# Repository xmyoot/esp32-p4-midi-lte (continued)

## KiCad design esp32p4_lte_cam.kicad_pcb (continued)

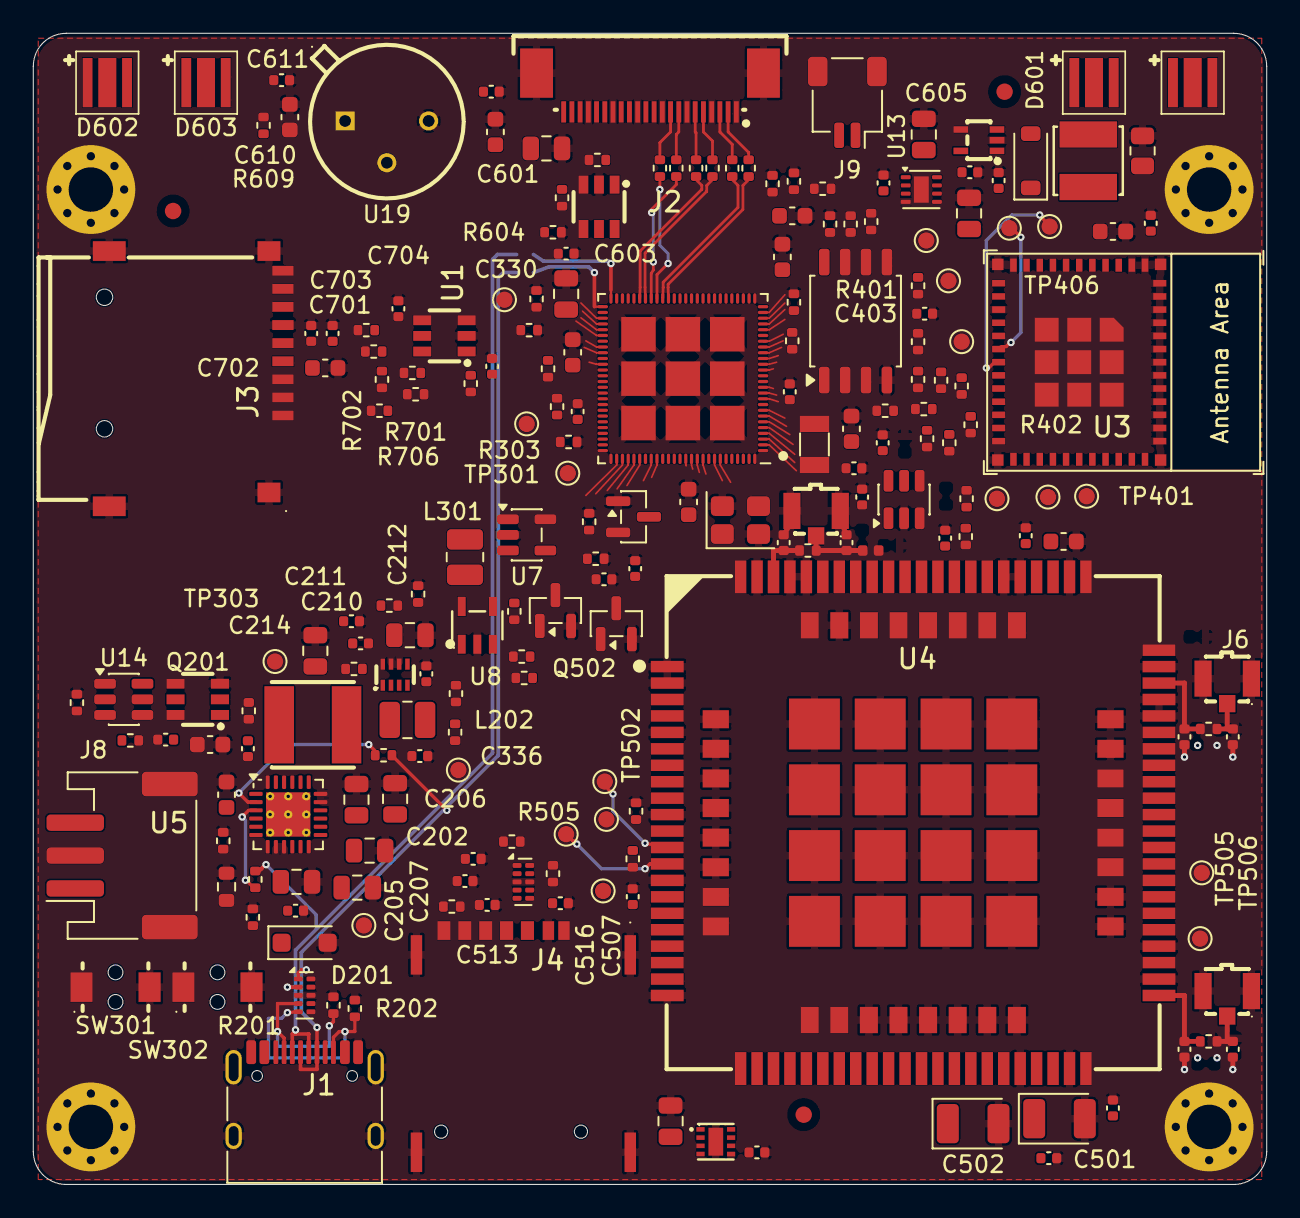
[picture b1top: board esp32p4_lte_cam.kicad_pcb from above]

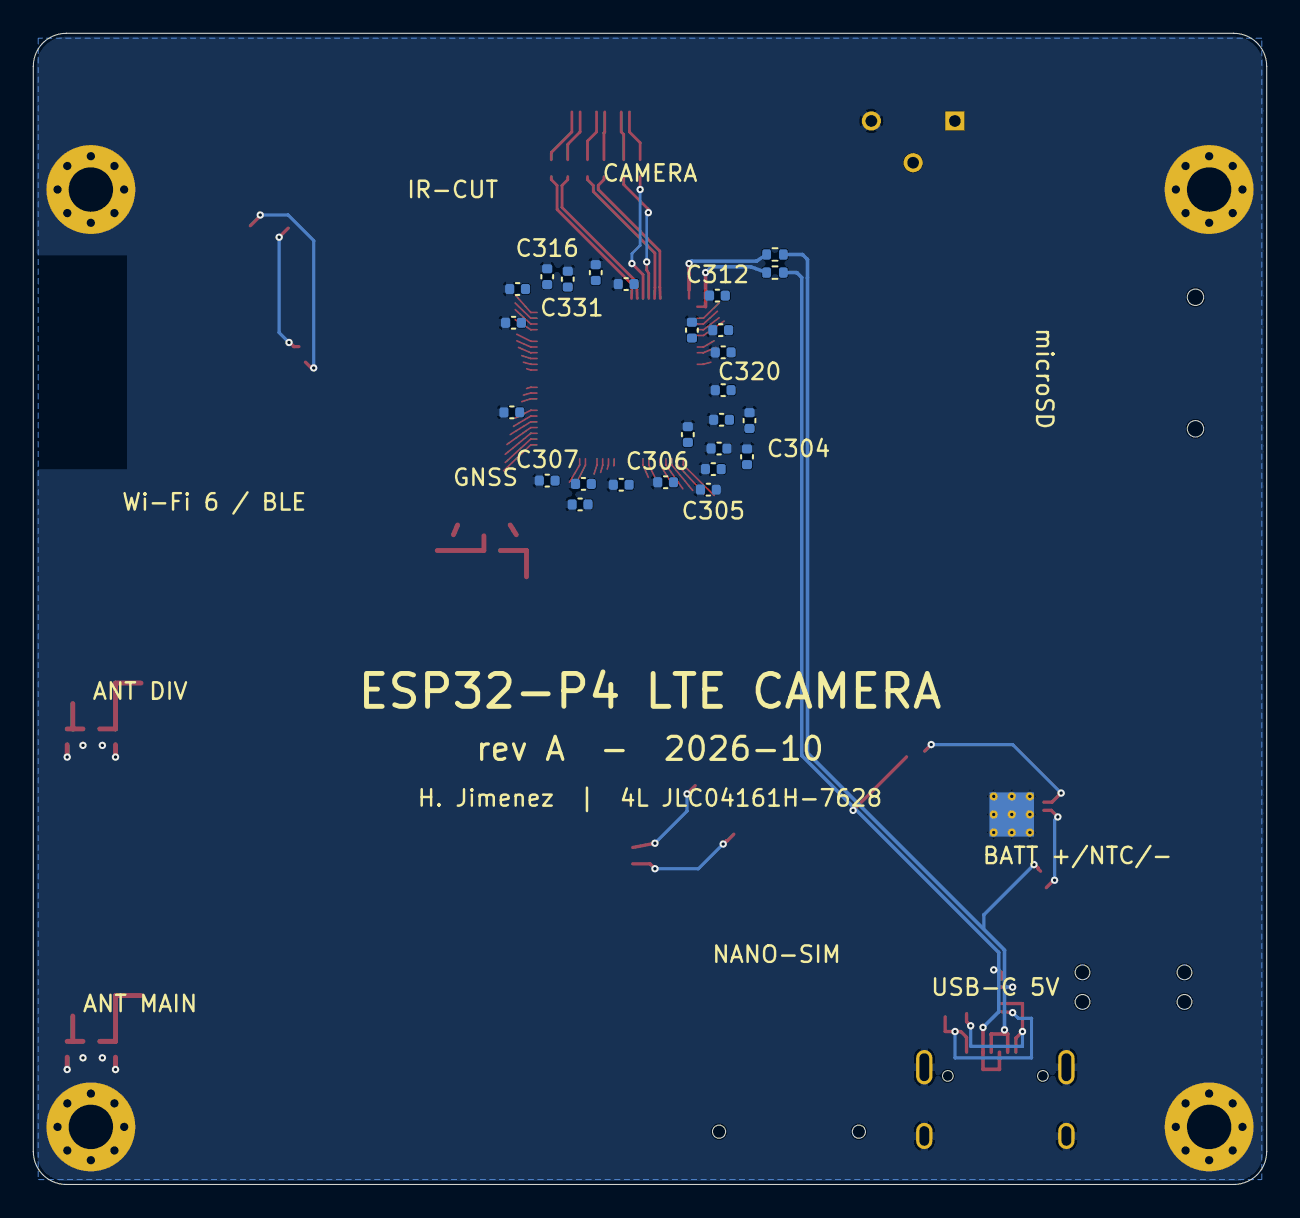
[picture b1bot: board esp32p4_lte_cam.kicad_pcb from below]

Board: 4 copper layers, 75.0 x 70.0 mm, 238 parts (26 on the bottom side), 160 nets.

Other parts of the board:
FID1, FID2, FID3: Fiducial; Fiducial_1mm_Mask2mm
H1, H2, H3, H4: M2.5; MountingHole_2.7mm_M2.5_Pad_Via

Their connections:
GND: H1.1, H2.1, H3.1, H4.1; also elsewhere on the board

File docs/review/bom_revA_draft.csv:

"Refs","Value","Footprint","LCSC","MPN","Qty","DNP"
"C201","1u 25V","Capacitor_SMD:C_0603_1608Metric","C5673","CL10A105KA8NNNC","1",""
"C202","10u 25V","Capacitor_SMD:C_0805_2012Metric","C15850","CL21A106KAYNNNE","1",""
"C203,C328,C610","4.7u 10V","Capacitor_SMD:C_0603_1608Metric","C1705","CL10A475KP8NNNC","3",""
"C204","47n 16V","Capacitor_SMD:C_0402_1005Metric","C307434","CL05B473KO5NNNC","1",""
"C205,C206,C207,C508,C605,C607","10u 10V","Capacitor_SMD:C_0805_2012Metric","C17024","CL21A106KPFNNNE","6",""
"C208,C213,C301,C302,C303,C304,C305,C306,C307,C311,C312,C313,C314,C317,C319,C320,C323,C326,C331,C336,C402,C504,C511,C512,C516,C602,C609,C611,C703","100n","Capacitor_SMD:C_0402_1005Metric","C1525","CL05B104KO5NNNC","29",""
"C209,C211,C212,C330","22u 10V","Capacitor_SMD:C_0805_2012Metric","C380338","TCC0805X5R226M100FT","4",""
"C214,C215,C316,C318,C321,C322,C325,C327,C403,C507,C604,C705","1u","Capacitor_SMD:C_0402_1005Metric","C52923","CL05A105KA5NQNC","12",""
"C308,C309,C310,C315,C401,C503,C601,C702","10u 10V","Capacitor_SMD:C_0603_1608Metric","C19702","CL10A106KP8NNNC","8",""
"C324","10n","Capacitor_SMD:C_0402_1005Metric","C15195","CL05B103KB5NNNC","1",""
"C329,C332,C333","22p","Capacitor_SMD:C_0402_1005Metric","C1555","0402CG220J500NT","3",""
"C334,C335","18p","Capacitor_SMD:C_0402_1005Metric","C1549","0402CG180J500NT","2",""
"C501,C502","220u 6.3V","Capacitor_Tantalum_SMD:CP_EIA-3528-21_Kemet-B","C30242","TLJB227M006R0500","2",""
"C505,C513,C514,C515","33p","Capacitor_SMD:C_0402_1005Metric","C1562","0402CG330J500NT","4",""
"C506","10p","Capacitor_SMD:C_0402_1005Metric","C32949","CL05C100JB5NNNC","1",""
"C509,C603,C704","1n 25V","Capacitor_SMD:C_0402_1005Metric","C541372","CC0402KRX7R8BB102","3",""
"C510,C608","100n 16V","Capacitor_SMD:C_0402_1005Metric","C1525","CL05B104KO5NNNC","2",""
"C606","4.7u 25V","Capacitor_SMD:C_0805_2012Metric","C1779","CL21A475KAQNNNE","1",""
"D201","SMF5.0A (TVS)","Diode_SMD:D_SOD-123F","C193402","SMF5.0A","1",""
"D601","B5819W","Diode_SMD:D_SOD-123","C8598","B5819W SL","1",""
"D602,D603,D604,D605","IR 850nm","lcsc:LED-SMD_3P-L3.8-W3.8_M3838E1IRS1G09","C2833567","M3838E1IRS1G09-850NM","4",""
"J1","USB-C (bottom edge)","Connector_USB:USB_C_Receptacle_HRO_TYPE-C-31-M-12","C165948","TYPE-C-31-M-12","1",""
"J2","CAM FPC 22P 0.5mm","lcsc:CONN-SMD_05B20L22P","C22459552","05B20L22P","1",""
"J3","microSD","lcsc:TF-SMD_TF-01A","C91145","TF-01A","1",""
"J4","Nano-SIM","lcsc:SIM-SMD_NANO-SIM-7P-H1.37","C7529384","NANO SIM 7P H1.37","1",""
"J5","U.FL MAIN","lcsc:RF-SMD_FRF05002-JSS103M","C88374","U.FL-R-SMT-1(80)","1",""
"J6","U.FL AUX","lcsc:RF-SMD_FRF05002-JSS103M","C88374","U.FL-R-SMT-1(80)","1",""
"J7","U.FL GNSS","lcsc:RF-SMD_FRF05002-JSS103M","C88374","U.FL-R-SMT-1(80)","1",""
"J8","BATT (+ / NTC / -)","Connector_JST:JST_PH_S3B-PH-SM4-TB_1x03-1MP_P2.00mm_Horizontal","C265101","S3B-PH-SM4-TB(LF)(SN)","1",""
"J9","IR-CUT","Connector_JST:JST_SH_SM02B-SRSS-TB_1x02-1MP_P1.00mm_Horizontal","C160402","SM02B-SRSS-TB(LF)(SN)","1",""
"L201","2.2uH","lcsc:IND-SMD_L5.0-W5.0_SMNR5030","C189797","SMNR5030-2R2N","1",""
"L202","1uH","Inductor_SMD:L_1008_2520Metric","C98348","WPN252012H1R0MT","1",""
"L301","2.2uH","Inductor_SMD:L_1008_2520Metric","C5832372","FTC252012S2R2MBCA","1",""
"L601","10uH","lcsc:IND-SMD_L4.0-W4.0","C38117","SWPA4030S100MT","1",""
"Q201","FS8205A","lcsc:SOT-23-6_L2.9-W1.6-P0.95-LS2.8-BR","C2830320","FS8205A","1",""
"Q501,Q502","2N7002","Package_TO_SOT_SMD:SOT-23","C8545","2N7002","2",""
"R201,R202","5.1k","Resistor_SMD:R_0402_1005Metric","C25905","0402WGF5101TCE","2",""
"R203,R204,R304,R305,R306,R307,R308,R309,R316,R317,R318,R319,R320,R321,R509,R510,R511","0","Resistor_SMD:R_0402_1005Metric","C17168","0402WGF0000TCE","17",""
"R205","120","Resistor_SMD:R_0402_1005Metric","C25079","0402WGF1200TCE","1",""
"R206","5.23k","Resistor_SMD:R_0402_1005Metric","C2933105","FRC0402F5231TS","1",""
"R207","30.1k","Resistor_SMD:R_0402_1005Metric","C29402","0402WGF3012TCE","1",""
"R208,R209,R210,R310,R312,R313,R401,R402,R403,R404,R405,R406,R407,R408,R508,R603,R702,R703,R704,R705,R706,R707","10k","Resistor_SMD:R_0402_1005Metric","C25744","0402WGF1002TCE","22",""
"R211,R609","100","Resistor_SMD:R_0402_1005Metric","C25076","0402WGF1000TCE","2",""
"R212,R311","1k","Resistor_SMD:R_0402_1005Metric","C11702","0402WGF1001TCE","2",""
"R213","560k","Resistor_SMD:R_0402_1005Metric","C137958","RC0402FR-07560KL","1",""
"R214,R501,R502,R503,R504,R605,R607,R608,R708","100k","Resistor_SMD:R_0402_1005Metric","C25741","0402WGF1003TCE","9",""
"R301","4.02k","Resistor_SMD:R_0402_1005Metric","C43251","0402WGF4021TCE","1",""
"R302,R303","499k","Resistor_SMD:R_0402_1005Metric","C2998054","FRC0402F4993TS","2",""
"R314,R315,R505,R506,R507,R701","22","Resistor_SMD:R_0402_1005Metric","C25092","0402WGF220JTCE","6",""
"R601,R602","2.2k","Resistor_SMD:R_0402_1005Metric","C25879","0402WGF2201TCE","2",""
"R606","0.68","Resistor_SMD:R_0805_2012Metric","C47389","0805W8F680LT5E","1",""
"SW301","RESET","lcsc:SW-SMD_L4.0-W2.9-P4.15-EH","C455278","TS-1088C-02026","1",""
"SW302","BOOT","lcsc:SW-SMD_L4.0-W2.9-P4.15-EH","C455278","TS-1088C-02026","1",""
"U1","ESP32-P4NRW32X","espressif:ESP32-P4","C54540373","ESP32-P4NRW32X","1",""
"U2","W25Q128JVSIQ","Package_SO:SOIC-8_5.3x5.3mm_P1.27mm","C97521","W25Q128JVSIQ","1",""
"U3","ESP32-C6-MINI-1","espressif:ESP32-C6-MINI-1","C5453904","ESP32-C6-MINI-1-N4","1",""
"U4","SIM7600G-H","lcsc:COMM-SMD_135P-L30.0-W30.0_SIM7600G","C5355477","SIM7600G-H","1",""
"U5","BQ25895RTWR","Package_DFN_QFN:Texas_RTW_WQFN-24-1EP_4x4mm_P0.5mm_EP2.7x2.7mm_ThermalVias","C80200","BQ25895RTWR","1",""
"U6","TPS631000","lcsc:SOT-583-8_L2.1-W1.2-P0.50-LS1.6-BL","C5219190","TPS631000DRLR","1",""
"U7","TLV62569","Package_TO_SOT_SMD:SOT-23-5","C141836","TLV62569DBVR","1",""
"U8","TPS7A0218","lcsc:SOT-23-5_L3.0-W1.7-P0.95-LS2.8-BL","C5144851","TPS7A0218DBVR","1",""
"U9","TPS22965","lcsc:UDFN-8_L2.0-W2.0-P0.50-TL-EP","C122837","TPS22965DSGR","1",""
"U10,U11","TPS22918","lcsc:SOT-23-6_L2.9-W1.6-P0.95-LS2.8-BR","C131941","TPS22918DBVR","2",""
"U12","TPS61169","lcsc:SC-70-5_L2.1-W1.3-P0.65-LS2.1-BR","C71045","TPS61169DCKR","1",""
"U13","DRV8837","Package_SON:Texas_DSG0008A_WSON-8-1EP_2x2mm_P0.5mm_EP0.9x1.6mm","C39159","DRV8837DSGR","1",""
"U14","DW01A","Package_TO_SOT_SMD:SOT-23-6","C351410","DW01A","1",""
"U15","TPS3839G33 (3.08V)","Package_TO_SOT_SMD:SOT-23","C485802","TPS3839G33DBZR","1",""
"U16","SN74LVC1T45","Package_TO_SOT_SMD:SOT-23-6","C7843","SN74LVC1T45DBVR","1",""
"U17,U18","TPD4E05U06","Package_SON:USON-10_2.5x1.0mm_P0.5mm","C138714","TPD4E05U06DQAR","2",""
"U19","XYC-PIR223D-S0","lcsc:TO-5-3_L8.2-W8.2","C2887901","XYC-PIR223D-S0","1",""
"Y1","40MHz 10ppm","Crystal:Crystal_SMD_3225-4Pin_3.2x2.5mm","C9010","X322540MPB4SI","1",""
"Y2","32.768kHz","Crystal:Crystal_SMD_3215-2Pin_3.2x1.5mm","C32346","Q13FC13500004","1",""

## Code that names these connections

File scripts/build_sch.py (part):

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s = D.sheet("mcu", "ESP32-P4 core - SoC, flash, clocks, core DC-DC, reset/boot")
s.notes += ["Chip rev v3.x (ESP32-P4NRW32X): VDD_HP_1 on pin 54; DC-DC feedback 499k/499k/22pF populated (HDG fig. 5).",
            "VDD_MIPI_DPHY fed from internal VDDO_3 (2.5 V) as on ESP32-P4-Function-EV v1.5.2. VDD_USBPHY unused (HS PHY not used).",
            "VDD_IO_6 = 1.8 V: GPIO49-54 talk to the SIM7600 UART natively. Keep these pins hi-Z while VBAT_LTE is off."]
u = s.add("U1", "espressif:ESP32-P4X", "ESP32-P4NRW32X", "espressif:ESP32-P4", LCSC="C54540373",
          MPN="ESP32-P4NRW32X", Note="Consigned - zero JLC stock at design time")
u.wire({  # power
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    "FLASH_CK": "P4_FL_CK", "FLASH_D": "P4_FL_D",
    "XTAL_N": "XTAL_N", "XTAL_P": "XTAL_P", "CHIP_PU": "CHIP_PU", "EN_DCDC": "EN_DCDC", "FB_DCDC": "FB_DCDC",
    # GPIO map (docs/ARCHITECTURE.md sec. 5)
    "GPIO0": "XTAL32_N", "GPIO1": "XTAL32_P", "GPIO2": "PIR_OUT", "GPIO3": "CHG_INT", "GPIO4": "MODEM_RI_3V3",
    "GPIO5": "SYS_SDA", "GPIO6": "SYS_SCL", "GPIO7": "MODEM_PWRKEY_CTL", "GPIO8": "MODEM_PWR_EN", "GPIO9": "C6_EN",
    "GPIO10": "C6_WAKE", "GPIO11": "MODEM_RESET_CTL", "GPIO12": "TP_GPIO12", "GPIO13": "TP_GPIO13",
    "GPIO14": "SDIO_D0", "GPIO15": "SDIO_D1", "GPIO16": "SDIO_D2", "GPIO17": "SDIO_D3", "GPIO18": "SDIO_CLK",
    "GPIO19": "SDIO_CMD", "GPIO20": "CAM_SDA", "GPIO21": "CAM_SCL", "GPIO22": "CAM_IO0", "GPIO23": "CAM_PWR_EN",
    "GPIO24": "P4_USB_DN", "GPIO25": "P4_USB_DP", "GPIO26": "C6_BOOT", "GPIO27": "IRCUT_NSLEEP",
    "GPIO28": "SD_PWR_EN", "GPIO29": "CAM_IO1", "GPIO30": "IRCUT_IN1", "GPIO31": "IRCUT_IN2", "GPIO32": "IR_LED_PWM",
    "GPIO33": "TP_GPIO33", "GPIO34": NC, "GPIO35": "BOOT", "GPIO36": NC, "GPIO37": "UART0_TX", "GPIO38": "UART0_RX",
    "GPIO39": "SD_D0", "GPIO40": "SD_D1", "GPIO41": "SD_D2", "GPIO42": "SD_D3", "GPIO43": "SD_CLK", "GPIO44": "SD_CMD",
    "GPIO45": "SD_DET", "GPIO46": NC, "GPIO47": NC, "GPIO48": NC,
    "GPIO49": "MDM_RXD", "GPIO50": "MDM_TXD", "GPIO51": "MDM_RTS", "GPIO52": "MDM_CTS", "GPIO53": "MDM_STATUS",
    "GPIO54": "MDM_DTR"})
# decoupling (HDG checklist sec. 1)
for net in ["3V3"] * 7:
    s.C("100n", net)
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s.R("22", "P4_USB_DP", "USB_DP"); s.R("22", "P4_USB_DN", "USB_DN")
for lane in ("D0_P", "D0_N", "CK_P", "CK_N", "D1_P", "D1_N"):
    s.R("0", f"P4_CSI_{lane}", f"CSI_{lane}")
for tp in ("UART0_TX", "UART0_RX", "BOOT", "CHIP_PU", "TP_GPIO12", "TP_GPIO13", "TP_GPIO33"):
    s.TP(tp)

# =====================================================================================  WIFI
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
# =====================================================================================  LTE
s = D.sheet("lte", "LTE Cat-4 + GNSS - SIM7600G-H, nano-SIM, antennas")
s.notes += ["VBAT_LTE from SYS via TPS22965 (16 mOhm). >=300 uF bulk at VBAT pins per SIMCom HW design sec. 3.1 (2 A GSM bursts).",
            "UART/STATUS/DTR are 1.8 V and connect straight to ESP32-P4 GPIO49-54 (VDD_IO_6 = 1V8_IO6).",
            "COEX1/COEX3/BOOT_CFG0 must not be pulled up before power-up -> left NC.  Pi-networks: series 0R, shunts DNP."]
u = s.add("U4", "lcsc:SIM7600G-H_C5355477", "SIM7600G-H", "lcsc:COMM-SMD_135P-L30.0-W30.0_SIM7600G", LCSC="C5355477",
          MPN="SIM7600G-H")
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
# =====================================================================================  STORAGE
s = D.sheet("storage", "microSD (SDMMC slot 0, 4-bit, 3.3 V) with power switch")
s.notes += ["SDMMC slot 0 fixed pins GPIO39-44; VDD_IO_5 at 3.3 V (no UHS-I). Pull-ups go to the switched rail 3V3_SD."]
s.add("J3", "lcsc:TF-01A", "microSD", "lcsc:TF-SMD_TF-01A", LCSC="C91145", MPN="TF-01A").wire(
    {"1": "SD_D2", "2": "SD_D3", "3": "SD_CMD", "4": "3V3_SD", "5": "SD_CLK_C", "6": "GND", "7": "SD_D0", "8": "SD_D1",
     "9": "SD_DET", "GND": "GND"})
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
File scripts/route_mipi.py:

"""Hand-designed MIPI CSI-2 routing (2 data lanes + clock), 100 ohm diff: w 0.17, s 0.13 (centres 0.30) on F.Cu over L2 GND.
Lane order differs between the ESP32-P4 (D1, CK, D0 with CK as N,P) and the Pi FPC (CK as P,N, D1, D0), and the P4 has no
documented lane/polarity remap, so the clock pair carries the crossover:
  CKP drops to B.Cu under its 0R (VP1); CKN crosses over it on F.Cu and drops (VN1); both run on B.Cu under the D1 pair,
  then return to F.Cu in a pocket between D1 and D0 (VN, VP, staggered) - now in P4 order (N left, P right).
D0 and D1 stay on F.Cu end to end.  Every coordinate below was clearance-checked against 0.127 mm; DRC verifies.
usage: $PY scripts/route_mipi.py board.kicad_pcb"""
import math, os, sys
import pcbnew

PCB = sys.argv[1]
b = pcbnew.LoadBoard(PCB)
MM = pcbnew.FromMM
W, HALF = 0.17, 0.15
VIA_D, VIA_DRILL = 0.45, 0.2
NETS = {k: b.FindNet(n) for k, n in [
    ("CKP", "CSI_CK_P"), ("CKN", "CSI_CK_N"), ("D1P", "CSI_D1_P"), ("D1N", "CSI_D1_N"), ("D0P", "CSI_D0_P"), ("D0N", "CSI_D0_N"),
    ("pCKP", "/mcu/P4_CSI_CK_P"), ("pCKN", "/mcu/P4_CSI_CK_N"), ("pD1P", "/mcu/P4_CSI_D1_P"), ("pD1N", "/mcu/P4_CSI_D1_N"),
    ("pD0P", "/mcu/P4_CSI_D0_P"), ("pD0N", "/mcu/P4_CSI_D0_N")]}

# wipe any earlier copper on these nets
for t in list(b.GetTracks()):
    if t.GetNetCode() in {n.GetNetCode() for n in NETS.values()}:
        b.Delete(t)


def pad(ref, net):
    for p in b.FindFootprintByReference(ref).Pads():
        if p.GetNetCode() == net.GetNetCode():
            q = p.GetPosition(); return pcbnew.ToMM(q.x), pcbnew.ToMM(q.y)
    raise KeyError((ref, net))


def seg(net, layer, pts, w=W):
    for (x0, y0), (x1, y1) in zip(pts, pts[1:]):
        if abs(x0 - x1) < 1e-6 and abs(y0 - y1) < 1e-6:
            continue
        t = pcbnew.PCB_TRACK(b); t.SetStart(pcbnew.VECTOR2I(MM(x0), MM(y0))); t.SetEnd(pcbnew.VECTOR2I(MM(x1), MM(y1)))
        t.SetWidth(MM(w)); t.SetLayer(layer); t.SetNet(net); b.Add(t)


def via(net, x, y):
    v = pcbnew.PCB_VIA(b); v.SetPosition(pcbnew.VECTOR2I(MM(x), MM(y))); v.SetWidth(MM(VIA_D)); v.SetDrill(MM(VIA_DRILL))
    v.SetNet(net); v.SetViaType(pcbnew.VIATYPE_THROUGH); b.Add(v)


def offset(poly, d):
    """Parallel offset of a polyline by d (positive = right of travel direction, y down), mitred corners."""
    out = []
    for i, (x, y) in enumerate(poly):
        ns = []
        for a, c in ((poly[i - 1], (x, y)) if i > 0 else (None, None), ((x, y), poly[i + 1]) if i < len(poly) - 1 else (None, None)):
            if a is None:
                continue
            dx, dy = c[0] - a[0], c[1] - a[1]; L = math.hypot(dx, dy); ns.append((-dy / L, dx / L))
        if len(ns) == 1:
            nx, ny = ns[0]; k = 1.0
        else:
            nx, ny = ns[0][0] + ns[1][0], ns[0][1] + ns[1][1]; L = math.hypot(nx, ny); nx, ny = nx / L, ny / L
            k = 1.0 / max(0.3, nx * ns[0][0] + ny * ns[0][1])
        out.append((x - nx * d * k, y - ny * d * k))
    return out


F, B = pcbnew.F_Cu, pcbnew.B_Cu
# ---------------- FPC -> 0R row (pad "2" of each 0R is the FPC side, on top)
for lane, ref in (("CKP", "R318"), ("CKN", "R319"), ("D1P", "R320"), ("D1N", "R321"), ("D0P", "R316"), ("D0N", "R317")):
    xf, yf = pad("J2", NETS[lane]); xr, yr = pad(ref, NETS[lane])
    y1 = yf + 1.22; seg(NETS[lane], F, [(xf, yf), (xf, y1), (xr, y1 + abs(xr - xf)), (xr, yr)])


# ---------------- data pairs on F.Cu: coupled centreline, P/N offset, terminal legs to the 0R and P4 pads
def pair(p_lane, n_lane, rp, rn, centre):
    P, N = NETS["p" + p_lane], NETS["p" + n_lane]
    (rpx, rpy), (rnx, rny) = pad(rp, P), pad(rn, N)
    (ppx, ppy), (pnx, pny) = pad("U1", P), pad("U1", N)
    a, c = offset(centre, HALF), offset(centre, -HALF)
    lp, ln = (a, c) if abs(a[-1][0] - ppx) < abs(c[-1][0] - ppx) else (c, a)
    seg(P, F, [(rpx, rpy), (rpx, rpy + 0.19), (lp[0][0], lp[0][1])] + lp + [(ppx, ppy)])
    seg(N, F, [(rnx, rny), (rnx, rny + 0.19), (ln[0][0], ln[0][1])] + ln + [(pnx, pny)])


pair("D1P", "D1N", "R320", "R321", [(40.8, 9.25), (40.8, 9.55), (37.05, 13.30), (37.05, 15.45)])
pair("D0P", "D0N", "R316", "R317", [(43.0, 9.25), (43.0, 10.65), (38.45, 15.20), (38.45, 15.45)])

# ---------------- clock pair: polarity + lane crossover
cp, cn = NETS["pCKP"], NETS["pCKN"]
(rpx, rpy), (rnx, rny) = pad("R318", cp), pad("R319", cn)
(ppx, ppy), (pnx, pny) = pad("U1", cp), pad("U1", cn)
VP1, VN1, VN, VP = (rpx, 9.5), (37.6, 10.9), (37.7, 13.9), (38.6, 14.0)
seg(cp, F, [(rpx, rpy), VP1]); via(cp, *VP1)
seg(cp, B, [VP1, (rpx, 12.9), (38.6, 13.4), VP]); via(cp, *VP)
seg(cp, F, [VP, (ppx, 14.675), (ppx, ppy)])
seg(cn, F, [(rnx, rny), (rnx, 9.2), (37.6, 10.7), VN1]); via(cn, *VN1)
seg(cn, B, [VN1, (37.7, 11.0), VN]); via(cn, *VN)
seg(cn, F, [VN, (37.7, 14.4), (pnx, 14.6), (pnx, pny)])

pcbnew.SaveBoard(PCB, b)


def length(net):
    return sum(pcbnew.ToMM(t.GetLength()) for t in b.GetTracks() if t.GetNetCode() == net.GetNetCode() and t.GetClass() == "PCB_TRACK")


print("lengths mm (FPC->0R | 0R->P4):")
for lane in ("CK", "D1", "D0"):
    lp = (length(NETS[lane + "P"]), length(NETS["p" + lane + "P"])); ln = (length(NETS[lane + "N"]), length(NETS["p" + lane + "N"]))
    print(f"  {lane}: P {lp[0]:.2f}+{lp[1]:.2f}={sum(lp):.2f}  N {ln[0]:.2f}+{ln[1]:.2f}={sum(ln):.2f}  skew {abs(sum(lp) - sum(ln)):.3f}")
sys.stdout.flush(); os._exit(0)
